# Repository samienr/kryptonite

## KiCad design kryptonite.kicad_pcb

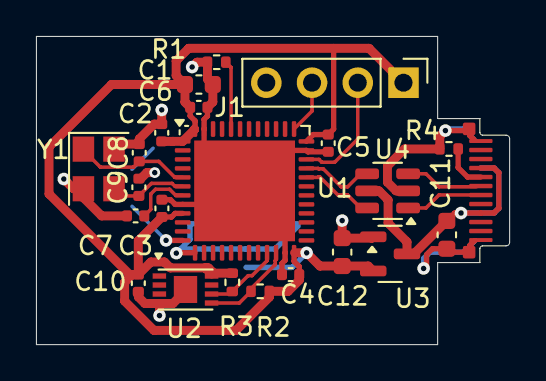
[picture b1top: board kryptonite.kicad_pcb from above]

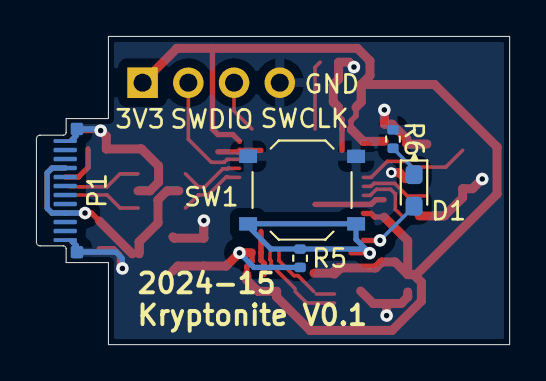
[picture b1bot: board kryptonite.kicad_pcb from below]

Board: 2 copper layers, 26.3 x 17.1 mm, 27 parts (4 on the bottom side), 17 nets.

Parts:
C1, C11, C12: 10u; C_0603_1608Metric
C2, C3, C4, C5, C6, C7, C10: 100n; C_0402_1005Metric
C8, C9: 33p; C_0402_1005Metric
D1: GR; LED_0603_1608Metric_Pad1.05x0.95mm_HandSolder
J1: Conn_01x04_Pin; PinHeader_1x04_P2.54mm_Vertical
P1: USB_C_Plug_USB2.0; TYPE-C-31-G-01
R1, R5: 10k; R_0402_1005Metric
R2, R3, R4: 4k7; R_0402_1005Metric
R6: 68; R_0402_1005Metric
SW1: SW_Push; SW_Push_1P1T_XKB_TS-1187A
U1: STM32F072CBUx; QFN-48-1EP_7x7mm_P0.5mm_EP5.6x5.6mm
U2: ATECC608B-MAHDA; DFN-8-1EP_3x2mm_P0.5mm_EP1.3x1.5mm
U3: MCP1700x-330xxTT; SOT-23
U4: USBLC6-2SC6; SOT-23-6
Y1: 8MHz; Crystal_SMD_3225-4Pin_3.2x2.5mm

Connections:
+3V3: C1.1, C2.1, C3.1, C4.1, C5.1, C6.1, C10.1, C12.1, J1.1, R2.1, R3.1, R5.2, U1.1 (VBAT), U1.9 (VDDA), U1.24 (VDD), U1.36 (VDDIO2), U1.48 (VDD), U2.8 (VCC), U3.2 (VO)
/BOOT0: R1.2, U1.44 (BOOT0)
/BTN: R5.1, SW1.1, U1.13 (PA3)
/HSE_IN: C8.1, U1.5 (PF0), Y1.1
/HSE_OUT: C9.1, U1.6 (PF1), Y1.3
/LED_A: D1.2 (A), U1.12 (PA2)
/LED_K: D1.1 (K), R6.2
/NRST: C7.2, U1.7 (NRST)
/SCL: R3.2, U1.21 (PB10), U2.6 (SCL)
/SDA: R2.2, U1.22 (PB11), U2.5 (SDA)
/SWCLK: J1.3, U1.37 (PA14)
/SWDIO: J1.2, U1.34 (PA13)
GND: C1.2, C2.2, C3.2, C4.2, C5.2, C6.2, C7.1, C8.2, C9.2, C10.2, C11.2, C12.2, J1.4, P1.A1 (GND), P1.A12 (GND), P1.B1 (GND), P1.B12 (GND), R1.1, R4.1, R6.1, SW1.2, U1.8 (VSSA), U1.23 (VSS), U1.35 (VSS), U1.47 (VSS), U1.49 (VSS), U2.4 (GND), U2.9 (EP), U3.1 (GND), U4.2 (GND), Y1.2, Y1.4
unnamed: P1.A5 (CC), R4.2
USB_D+: U1.33 (PA12), U4.4 (I/O2)
USB_D-: U1.32 (PA11), U4.6 (I/O1)
VBUS: C11.1, P1.A4 (VBUS), P1.A9 (VBUS), P1.B4 (VBUS), P1.B9 (VBUS), U3.3 (VI), U4.5 (VBUS)

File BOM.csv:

"Reference","Value","Footprint","Qty","Manufacturer","Manufacturer Part Number","Distributer Link"
"C1,C11,C12","10u","Capacitor_SMD:C_0603_1608Metric","3","","",""
"C2,C3,C4,C5,C6,C7,C10","100n","Capacitor_SMD:C_0402_1005Metric","7","","",""
"C8,C9","33p","Capacitor_SMD:C_0402_1005Metric","2","","",""
"D1","GR","LED_SMD:LED_0603_1608Metric_Pad1.05x0.95mm_HandSolder","1","XINGLIGHT","XL-1608SURC-06","https://www.lcsc.com/product-detail/Light-Emitting-Diodes-LE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"
"J1","Conn_01x04_Pin","Connector_PinHeader_2.54mm:PinHeader_1x04_P2.54mm_Vertical","1","CONNFLY","DS1021-1x4SF11-B","https://www.lcsc.com/product-detail/Pin-Headers_CONNFLY-Elec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"
"P1","USB_C_Plug_USB2.0","type-c:TYPE-C-31-G-01","1","  Korean Hroparts Elec","TYPE-C-31-G-01","https://www.lcsc.com/product-detail/USB-Connectors_Korean-Hr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"
"R1,R5","10k","Resistor_SMD:R_0402_1005Metric","2","YAGEO","RC0402FR-0710KL","https://www.lcsc.com/product-detail/Chip-Resistor-Surface-Mo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"
"R2,R3,R4","4k7","Resistor_SMD:R_0402_1005Metric","3","UNI-ROYAL(Uniroyal Elec)","0402WGJ0472TCE","https://www.lcsc.com/product-detail/Chip-Resistor-Surface-Mo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"
"R6","68","Resistor_SMD:R_0402_1005Metric","1","FOJAN","FRC0402J680 TS","https://www.lcsc.com/product-detail/Chip-Resistor-Surface-Mo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"
"SW1","SW_Push","Button_Switch_SMD:SW_Push_1P1T_XKB_TS-1187A","1","XKB Connection","TS-1187A-B-A-B","https://www.lcsc.com/product-detail/Tactile-Switches_XKB-Con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"
"U1","STM32F072CBUx","Package_DFN_QFN:QFN-48-1EP_7x7mm_P0.5mm_EP5.6x5.6mm","1","STMicroelectronics","STM32F072CBU6","https://www.lcsc.com/product-detail/Microcontrollers-MCU-MPU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"
"U2","ATECC608B-MAHDA","Package_DFN_QFN:DFN-8-1EP_3x2mm_P0.5mm_EP1.3x1.5mm","1","Microchip Tech","ATECC608B-MAHDA-S","https://www.lcsc.com/product-detail/Security-Verification-En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"
"U3","MCP1700x-330xxTT","Package_TO_SOT_SMD:SOT-23","1","Microchip Tech","MCP1700T-3302E/TT","https://www.lcsc.com/product-detail/Voltage-Regulators-Linea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"
"U4","USBLC6-2SC6","Package_TO_SOT_SMD:SOT-23-6","1","STMicroelectronics","USBLC6-2SC6","https://www.lcsc.com/product-detail/ESD-and-Surge-Protection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"
"Y1","8MHz","Crystal:Crystal_SMD_3225-4Pin_3.2x2.5mm","1","Yajingxin","TAXM8M4RLBDDT2T","https://www.lcsc.com/product-detail/Crystals_Yajingxin-TAXM8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"

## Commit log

2024-07-08 Added ESD protection
2024-07-12 did some stuff
2024-07-16 Finalized PCB layout and added gerbers
2024-07-16 Added component placement
2024-07-16 Added gerbers and drills
